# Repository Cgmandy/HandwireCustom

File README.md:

# HandwireCustom
 Custom keyboard with handwired components

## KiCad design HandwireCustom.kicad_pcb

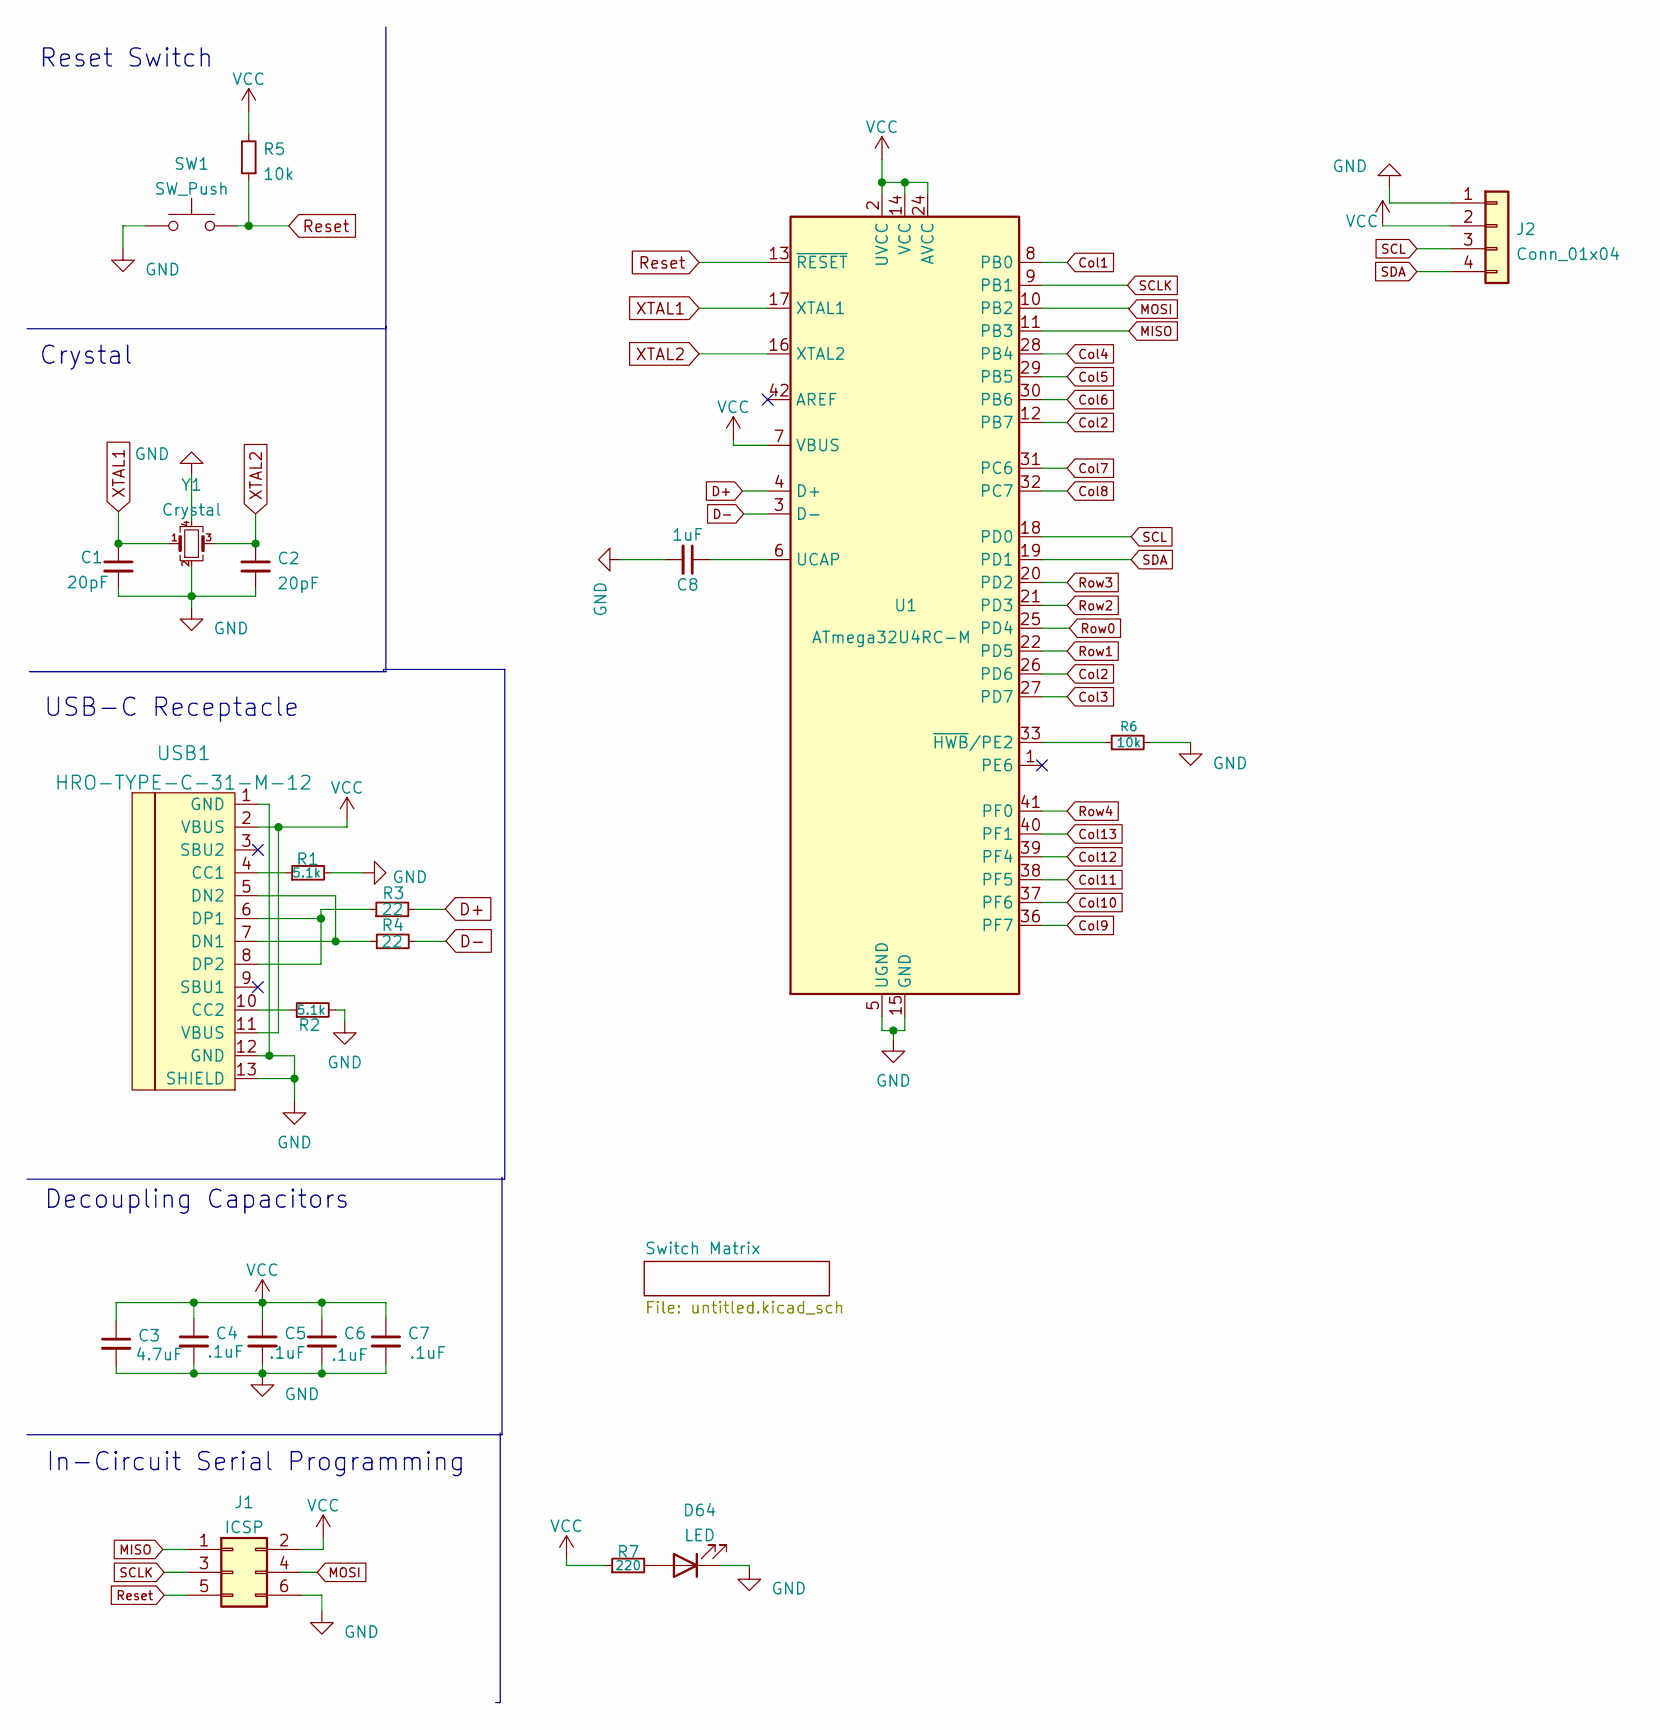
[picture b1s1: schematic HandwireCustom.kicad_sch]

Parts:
C1, C2: 20pF; C_0402_1005Metric
C3: 4.7uF; C_Disc_D4.3mm_W1.9mm_P5.00mm
C4, C5, C6, C7: .1uF; C_0402_1005Metric
C8: 1uF; C_0402_1005Metric
D64: LED; LED_D3.0mm_Clear
J1: ICSP; PinHeader_2x03_P2.54mm_Vertical
J2: Conn_01x04; PinHeader_1x04_P2.54mm_Vertical
R1, R2: 5.1k; R_0402_1005Metric
R3, R4: 22; R_0402_1005Metric
R5: 10k; R_Axial_DIN0204_L3.6mm_D1.6mm_P5.08mm_Horizontal
R6: 10k; R_0402_1005Metric
R7: 220; R_Axial_DIN0204_L3.6mm_D1.6mm_P5.08mm_Horizontal
SW1: SW_Push; SW_PUSH_6mm
U1: ATmega32U4RC-M; QFN-44-1EP_7x7mm_P0.5mm_EP5.2x5.2mm
USB1: HRO-TYPE-C-31-M-12; HRO-TYPE-C-31-M-12-Assembly
Y1: Crystal; Crystal_SMD_3225-4Pin_3.2x2.5mm

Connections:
Col1: U1.8 (PB0); also elsewhere on the board
Col3: U1.27 (PD7); also elsewhere on the board
Col4: U1.28 (PB4); also elsewhere on the board
Col5: U1.29 (PB5); also elsewhere on the board
Col6: U1.30 (PB6); also elsewhere on the board
Col7: U1.31 (PC6); also elsewhere on the board
Col8: U1.32 (PC7); also elsewhere on the board
Col9: U1.36 (PF7); also elsewhere on the board
Col10: U1.37 (PF6); also elsewhere on the board
Col11: U1.38 (PF5); also elsewhere on the board
Col12: U1.39 (PF4); also elsewhere on the board
Col13: U1.40 (PF1); also elsewhere on the board
D+: R3.2, U1.4 (D+)
D-: R4.2, U1.3 (D-)
GND: C1.2, C2.2, C3.2, C4.2, C5.2, C6.2, C7.2, C8.2, D64.1 (K), J1.6, J2.1, R1.2, R2.2, R6.2, SW1.1, U1.5 (UGND), U1.15 (GND), U1.23 (GND), U1.35 (GND), U1.43 (GND), U1.45 (GND), USB1.1 (GND), USB1.12 (GND), USB1.13 (SHIELD), Y1.2, Y1.4
MISO: J1.1, U1.11 (PB3)
MOSI: J1.4, U1.10 (PB2)
unnamed: C8.1, U1.6 (UCAP)
unnamed: D64.2 (A), R7.2
unnamed: R1.1, USB1.4 (CC1)
unnamed: R2.1, USB1.10 (CC2)
unnamed: R3.1, USB1.6 (DP1), USB1.8 (DP2)
unnamed: R4.1, USB1.5 (DN2), USB1.7 (DN1)
unnamed: R6.1, U1.33 (~HWB/PE2)
Reset: J1.5, R5.1, SW1.2, U1.13 (~RESET)
Row0: U1.25 (PD4); also elsewhere on the board
Row1: U1.22 (PD5); also elsewhere on the board
Row2: U1.21 (PD3); also elsewhere on the board
Row3: U1.20 (PD2); also elsewhere on the board
Row4: U1.41 (PF0); also elsewhere on the board
SCL: J2.3, U1.18 (PD0)
SCLK: J1.3, U1.9 (PB1)
SDA: J2.4, U1.19 (PD1)
VCC: C3.1, C4.1, C5.1, C6.1, C7.1, J1.2, J2.2, R5.2, R7.1, U1.2 (UVCC), U1.7 (VBUS), U1.14 (VCC), U1.24 (AVCC), U1.34 (VCC), U1.44 (AVCC), USB1.2 (VBUS), USB1.11 (VBUS)
XTAL1: C1.1, U1.17 (XTAL1), Y1.1
XTAL2: C2.1, U1.16 (XTAL2), Y1.3

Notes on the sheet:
USB-C Receptacle
Decoupling Capacitors
Crystal
In-Circuit Serial Programming
Reset Switch

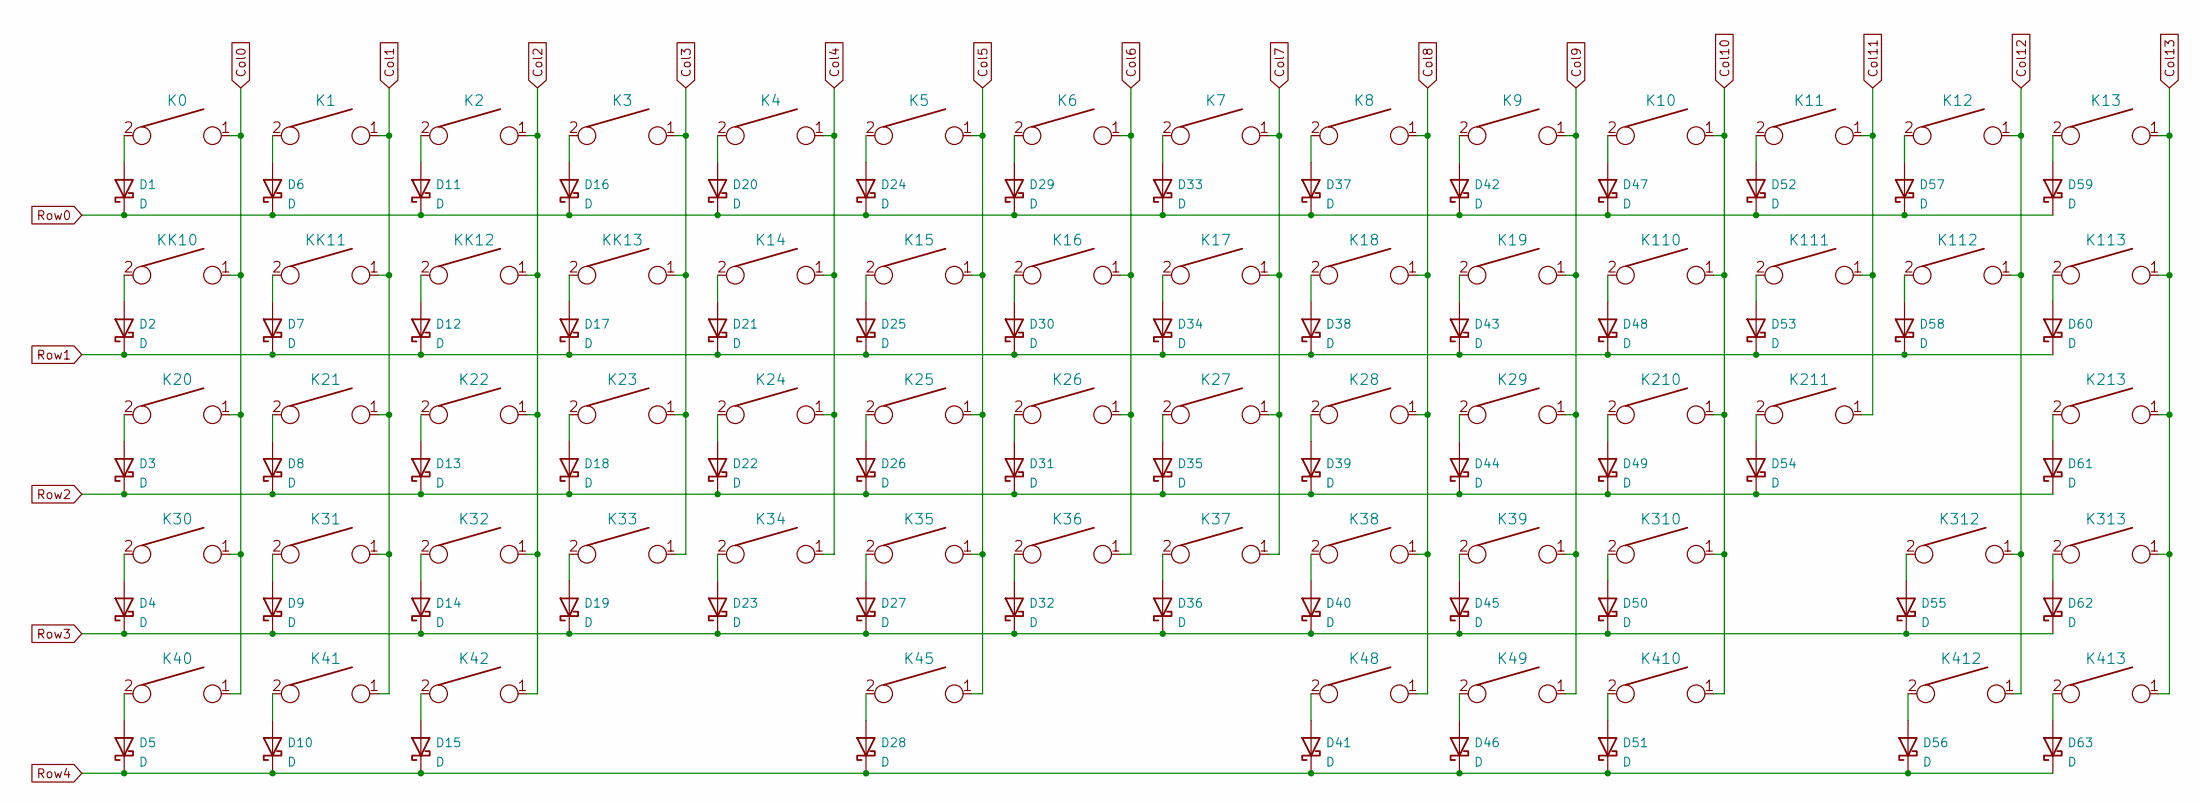
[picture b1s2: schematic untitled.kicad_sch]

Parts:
D1, D2, D3, D4, D5, D6, D7, D8, D9, D10, D11, D12, D13, D14, D15, D16, D17, D18, D19, D20, D21, D22, D23, D24, D25, D26, D27, D28, D29, D30, D31, D32, D33, D34, D35, D36, D37, D38, D39, D40, D41, D42, D43, D44, D45, D46, D47, D48, D49, D50, D51, D52, D53, D54, D55, D56, D57, D58, D59, D60, D61, D62, D63: D; D_DO-35_SOD27_P7.62mm_Horizontal
K0, K1, K2, K3, K4, K5, K6, K7, K8, K9, K10, K11, K12, K14, K15, K16, K17, K18, K19, K21, K22, K23, K24, K25, K26, K27, K28, K29, K31, K32, K33, K34, K35, K36, K37, K38, K39, K48, K49, K110, K111, K112, K210, K211, K312, K313, K410, K412, K413: KEYSW; MXOnly-1U-Hotswap
K13: KEYSW; MXOnly-2U-Hotswap
K20, K310: KEYSW; MXOnly-1.75U-Hotswap
K30, K213: KEYSW; MXOnly-2.25U-Hotswap
K40, K41, K42: KEYSW; MXOnly-1.25U-Hotswap
K45: KEYSW; MXOnly-6.25U-Hotswap-ReversedStabilizers
K113: KEYSW; MXOnly-1.5U-Hotswap
KK10: KEYSW; MXOnly-1.5U-Hotswap
KK11, KK12, KK13: KEYSW; MXOnly-1U-Hotswap

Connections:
Col1: K1.1, K21.1, K31.1, K41.1, KK11.1; also elsewhere on the board
Col3: K3.1, K23.1, K33.1, KK13.1; also elsewhere on the board
Col4: K4.1, K14.1, K24.1, K34.1; also elsewhere on the board
Col5: K5.1, K15.1, K25.1, K35.1, K45.1; also elsewhere on the board
Col6: K6.1, K16.1, K26.1, K36.1; also elsewhere on the board
Col7: K7.1, K17.1, K27.1, K37.1; also elsewhere on the board
Col8: K8.1, K18.1, K28.1, K38.1, K48.1; also elsewhere on the board
Col9: K9.1, K19.1, K29.1, K39.1, K49.1; also elsewhere on the board
Col10: K10.1, K110.1, K210.1, K310.1, K410.1; also elsewhere on the board
Col11: K11.1, K111.1, K211.1; also elsewhere on the board
Col12: K12.1, K112.1, K312.1, K412.1; also elsewhere on the board
Col13: K13.1, K113.1, K213.1, K313.1, K413.1; also elsewhere on the board
unnamed: D1.2 (A), K0.2
unnamed: D2.2 (A), KK10.2
unnamed: D3.2 (A), K20.2
unnamed: D4.2 (A), K30.2
unnamed: D5.2 (A), K40.2
unnamed: D6.2 (A), K1.2
unnamed: D7.2 (A), KK11.2
unnamed: D8.2 (A), K21.2
unnamed: D9.2 (A), K31.2
unnamed: D10.2 (A), K41.2
unnamed: D11.2 (A), K2.2
unnamed: D12.2 (A), KK12.2
unnamed: D13.2 (A), K22.2
unnamed: D14.2 (A), K32.2
unnamed: D15.2 (A), K42.2
unnamed: D16.2 (A), K3.2
unnamed: D17.2 (A), KK13.2
unnamed: D18.2 (A), K23.2
unnamed: D19.2 (A), K33.2
unnamed: D20.2 (A), K4.2
unnamed: D21.2 (A), K14.2
unnamed: D22.2 (A), K24.2
unnamed: D23.2 (A), K34.2
unnamed: D24.2 (A), K5.2
unnamed: D25.2 (A), K15.2
unnamed: D26.2 (A), K25.2
unnamed: D27.2 (A), K35.2
unnamed: D28.2 (A), K45.2
unnamed: D29.2 (A), K6.2
unnamed: D30.2 (A), K16.2
unnamed: D31.2 (A), K26.2
unnamed: D32.2 (A), K36.2
unnamed: D33.2 (A), K7.2
unnamed: D34.2 (A), K17.2
unnamed: D35.2 (A), K27.2
unnamed: D36.2 (A), K37.2
unnamed: D37.2 (A), K8.2
unnamed: D38.2 (A), K18.2
unnamed: D39.2 (A), K28.2
unnamed: D40.2 (A), K38.2
unnamed: D41.2 (A), K48.2
unnamed: D42.2 (A), K9.2
unnamed: D43.2 (A), K19.2
unnamed: D44.2 (A), K29.2
unnamed: D45.2 (A), K39.2
unnamed: D46.2 (A), K49.2
unnamed: D47.2 (A), K10.2
unnamed: D48.2 (A), K110.2
unnamed: D49.2 (A), K210.2
unnamed: D50.2 (A), K310.2
unnamed: D51.2 (A), K410.2
unnamed: D52.2 (A), K11.2
unnamed: D53.2 (A), K111.2
unnamed: D54.2 (A), K211.2
unnamed: D55.2 (A), K312.2
unnamed: D56.2 (A), K412.2
unnamed: D57.2 (A), K12.2
unnamed: D58.2 (A), K112.2
unnamed: D59.2 (A), K13.2
unnamed: D60.2 (A), K113.2
unnamed: D61.2 (A), K213.2
unnamed: D62.2 (A), K313.2
unnamed: D63.2 (A), K413.2
Row0: D1.1 (K), D6.1 (K), D11.1 (K), D16.1 (K), D20.1 (K), D24.1 (K), D29.1 (K), D33.1 (K), D37.1 (K), D42.1 (K), D47.1 (K), D52.1 (K), D57.1 (K), D59.1 (K); also elsewhere on the board
Row1: D2.1 (K), D7.1 (K), D12.1 (K), D17.1 (K), D21.1 (K), D25.1 (K), D30.1 (K), D34.1 (K), D38.1 (K), D43.1 (K), D48.1 (K), D53.1 (K), D58.1 (K), D60.1 (K); also elsewhere on the board
Row2: D3.1 (K), D8.1 (K), D13.1 (K), D18.1 (K), D22.1 (K), D26.1 (K), D31.1 (K), D35.1 (K), D39.1 (K), D44.1 (K), D49.1 (K), D54.1 (K), D61.1 (K); also elsewhere on the board
Row3: D4.1 (K), D9.1 (K), D14.1 (K), D19.1 (K), D23.1 (K), D27.1 (K), D32.1 (K), D36.1 (K), D40.1 (K), D45.1 (K), D50.1 (K), D55.1 (K), D62.1 (K); also elsewhere on the board
Row4: D5.1 (K), D10.1 (K), D15.1 (K), D28.1 (K), D41.1 (K), D46.1 (K), D51.1 (K), D56.1 (K), D63.1 (K); also elsewhere on the board

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
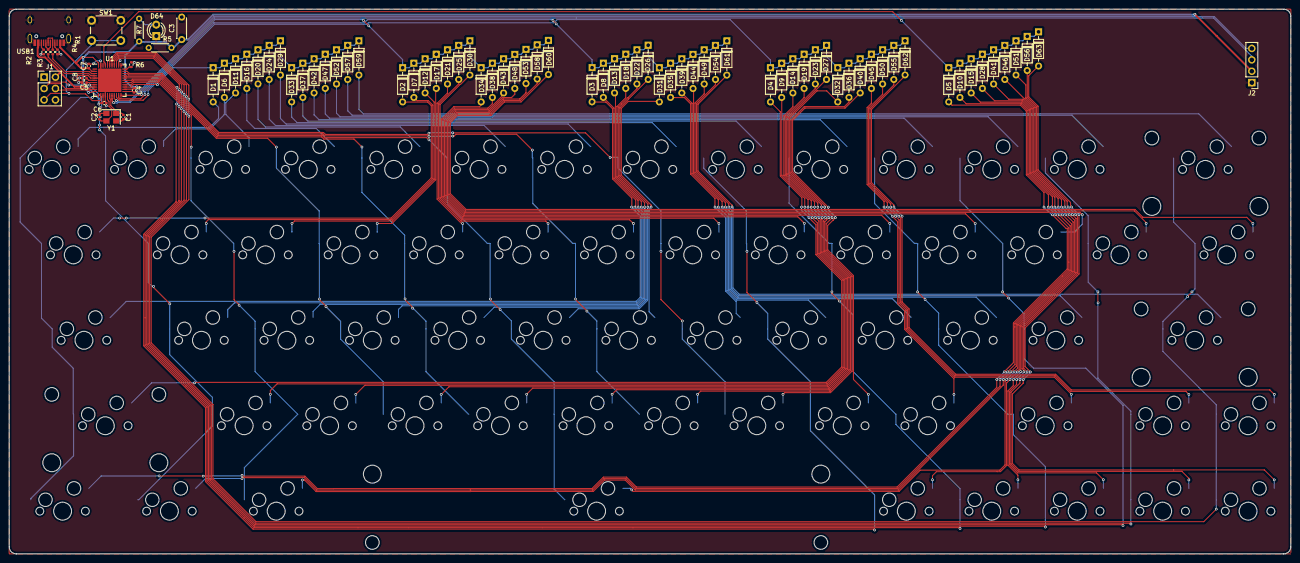
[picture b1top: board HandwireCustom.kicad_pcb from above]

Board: 2 copper layers, 285.8 x 121.4 mm, 148 parts (0 on the bottom side), 101 nets.

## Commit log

2022-01-09 2nd row done
2022-01-10 Completed
    DRC: 0 Errors, 0 Warnings
2022-01-10 Filled ground planes
2022-01-10 Pull-up Resistors Added
2022-01-10 Ready for JLCPCB
2022-09-10 Rerouted, new parts
